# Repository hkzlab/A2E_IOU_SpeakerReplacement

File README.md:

# Apple //e IOU IOU Prosthetic Speaker Board

## Introduction

**NOTE:** While I'm pretty sure my prototype works and is wired like the schematics you find in this project, I've yet to receive the PCBs from the producers and test them. I will remove this warning once I'll be able to test one.

While the original Apple ][ computers where completely built out of off-the-shelf integrated circuits, the newer "enhanced" units (//e, ][e) used custom ICs (IOU and MMU) to replace a lot of the old logic. This was done both as a cost cutting measure and as a way to hinder the creation of clones.

A side effect is that these custom ICs are nowadays almost impossible to obtain, and if one of them dies, you're left short of an Apple //e.

During the repair of a //e, I noticed that all the self-tests were passing, but there was no audible beep coming from the speaker. After investigating the source of the Issue, I found out that the speaker was driven by the `SPKR` signal coming from PIN 8 of the IOU, and that pin was only producing noise.

Instead of scrapping the board for parts, I decided to reimplement the logic in the IOU that triggers the speaker: a flip-flop that pilots an open-collector output and gets clocked when when the CPU accesses address `$C03x`.

### How does it work

This board gets sandwiched between the IOU and the motherboard, it leeches the signals required to decode the `SPKR` signal and then feeds it back to the mainboard. The pin 8 of the IOU that provided the original signal becomes isolated.

U2 (74LS373) is used to latch the addresses A3, A4 and A7, effectively demultiplexing them.

U1 provides the following functions: It implements the latch signal that gets fed into U2 so it can demultiplex the address lines, it implements a flip flop that gets triggered when an address in range `$C03x` gets accessed, and finally it implements an OC output enabled or disabled by the flip-flop, that will be used to pull low the speaker line.

## BOM

- 2x rows of 20-pin male headers turned pins
- 1x 40-pin wide socket
- 1x 74LS373 (U2)
- 1x GAL16V8 (U1)
- 2x 100nF ceramic capacitors (mount these on the __underside__ of the board)

With the top of the board facing you, the male headers must be installed in the 1st and 3rd column, with the pins facing the underside of the board, so they can be inserted into a socket in the mainboard.

Remember to flash the JED file to the GAL16V8!

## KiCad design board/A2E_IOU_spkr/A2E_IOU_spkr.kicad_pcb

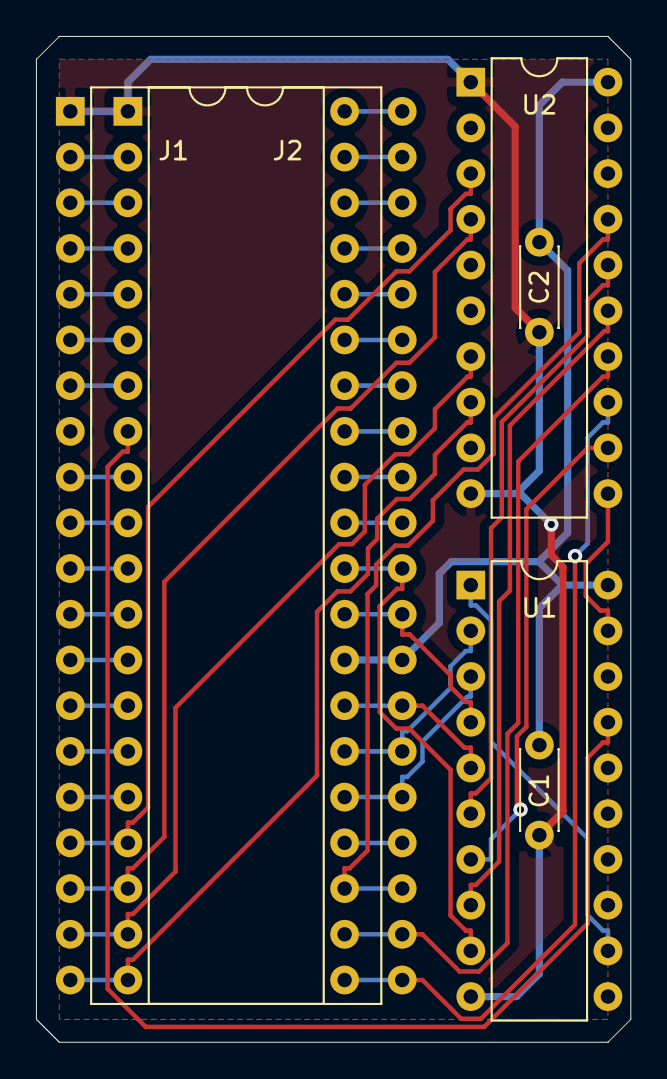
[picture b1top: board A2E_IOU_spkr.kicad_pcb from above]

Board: 2 copper layers, 33.0 x 55.9 mm, 6 parts (0 on the bottom side), 45 nets.

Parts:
C1, C2: 100nF; C_Disc_D4.3mm_W1.9mm_P5.00mm
J1: IOU_Socket; DIP-40_W15.24mm
J2: PCB_Socket; DIP-40_W15.24mm
U1: GAL16V8; DIP-20_W7.62mm
U2: 74LS373; DIP-20_W7.62mm

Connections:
/A6: J1.29, J2.29, U1.4
/ADDR_LATCH: U1.19, U2.11
/AN0: J1.10, J2.10
/AN1: J1.11, J2.11
/AN2: J1.12, J2.12
/AN3: J1.13, J2.13
/CASS0: J1.7, J2.7
/H0: J1.40, J2.40
/IAKD: J1.31, J2.31
/IKSTRB: J1.32, J2.32
/LA4: U1.7, U2.12
/LA5: U1.8, U2.15
/LA7: U1.6, U2.16
/LGR: J1.2, J2.2
/MD7: J1.9, J2.9
/N_SPKR: J2.8, U1.17
/ORA0: J1.17, J2.17, U2.3
/ORA1: J1.18, J2.18, U2.4
/ORA2: J1.19, J2.19, U2.7
/ORA3: J1.20, J2.20, U2.8
/ORA4: J1.21, J2.21, U2.13
/ORA5: J1.22, J2.22, U2.14
/ORA6: J1.23, J2.23, U2.17
/ORA7: J1.24, J2.24
/PHI0: J1.26, J2.26, U1.2
/Q3: J1.27, J2.27, U1.5
/RW: J1.14, J2.14
/SEGA: J1.3, J2.3
/SEGB: J1.4, J2.4
/SEGC: J1.5, J2.5
/VID6: J1.34, J2.34
/VID7: J1.33, J2.33
/~80COL: J1.6, J2.6
/~C0XX: J1.30, J2.30, U1.9
/~CLRGAT: J1.37, J2.37
/~IRQ: J1.16, J2.16
/~PRAS: J1.25, J2.25, U1.3
/~RA9: J1.35, J2.35
/~RAI0: J1.36, J2.36
/~RESET: J1.15, J2.15
/~SYNC: J1.39, J2.39
/~WNDW: J1.38, J2.38
GND: C1.2, C2.2, J1.1, J2.1, U1.10, U2.1, U2.10
unnamed: U1.1, U1.12
VCC: C1.1, C2.1, J1.28, J2.28, U1.20, U2.20

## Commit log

2020-10-18 Add kicad files
2020-10-18 Base pcb for GAL
2020-10-18 Add EQN gal
2020-10-18 Update eqn and schematics
2020-10-18 Update PCB
2020-10-19 Update PLD
2020-10-19 Another PLD update
2020-10-19 Add gerbers
2020-10-19 Update schematics
2020-10-19 New GAL pld
2020-10-20 Update PLD to use an external latch
2020-10-20 Updated PCB
2020-10-20 Cleanup schematics
2020-10-20 Add the JED file
2020-10-20 Add README
2020-10-20 Add pdf
2020-10-20 Updated the README
2020-10-21 Updated the PLD
2021-11-09 Replace kicad-pcb with kicad.org
